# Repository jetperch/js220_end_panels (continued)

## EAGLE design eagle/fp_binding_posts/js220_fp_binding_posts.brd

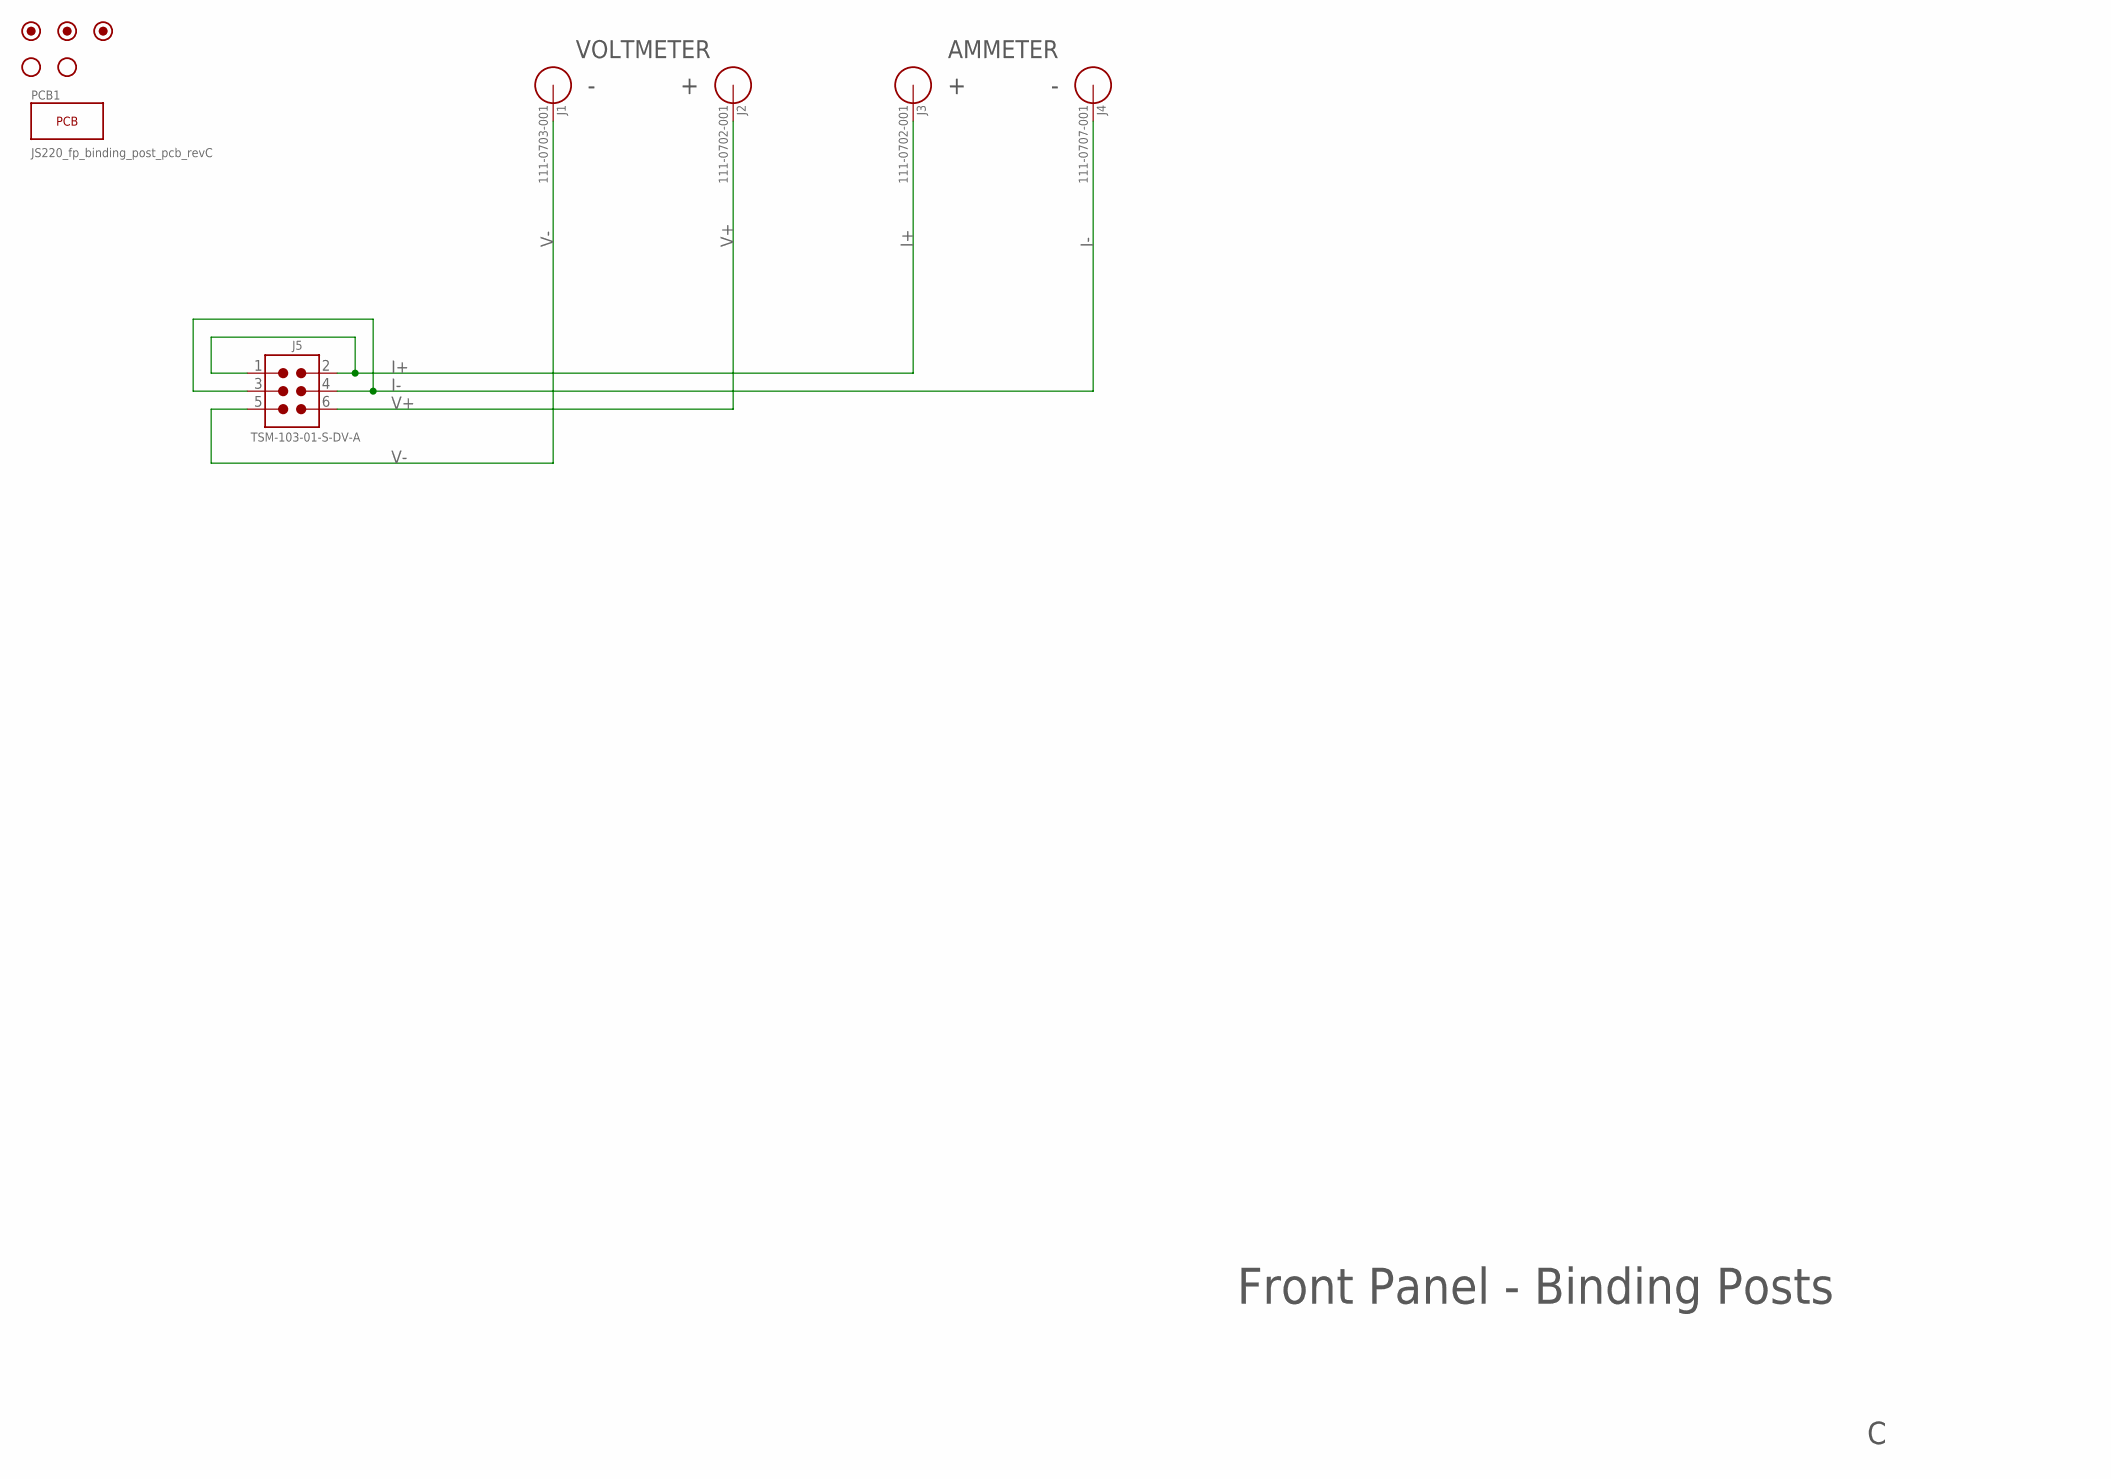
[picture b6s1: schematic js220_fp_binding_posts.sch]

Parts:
FUD1, FUD2, FUD3: FIDUCIAL_1MM; FIDUCIAL_1MM_2MM
H1, H2: HOLE_#6_NORESTRICT; HOLE_3.5MM_NORESTRICT
J1: 111-0703-001; BINDING_POST_6; MPN 111-0703-001
J2, J3: 111-0702-001; BINDING_POST_6; MPN 111-0702-001
J4: 111-0707-001; BINDING_POST_6; MPN 111-0707-001
J5: TSM-103-01-S-DV-A; CONN_0.1_3X2_MSA; MPN TSM-103-01-S-DV-A

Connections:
I+: J3.1, J5.1, J5.2
I-: J4.1, J5.3, J5.4
V+: J2.1, J5.6
V-: J1.1, J5.5

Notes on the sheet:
Front Panel - Binding Posts
+ -
AMMETER
VOLTMETER
- +

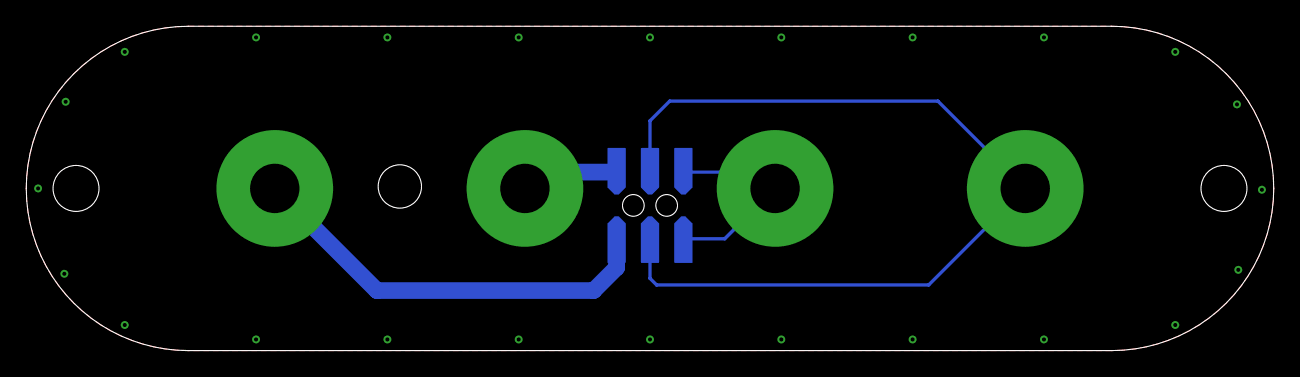
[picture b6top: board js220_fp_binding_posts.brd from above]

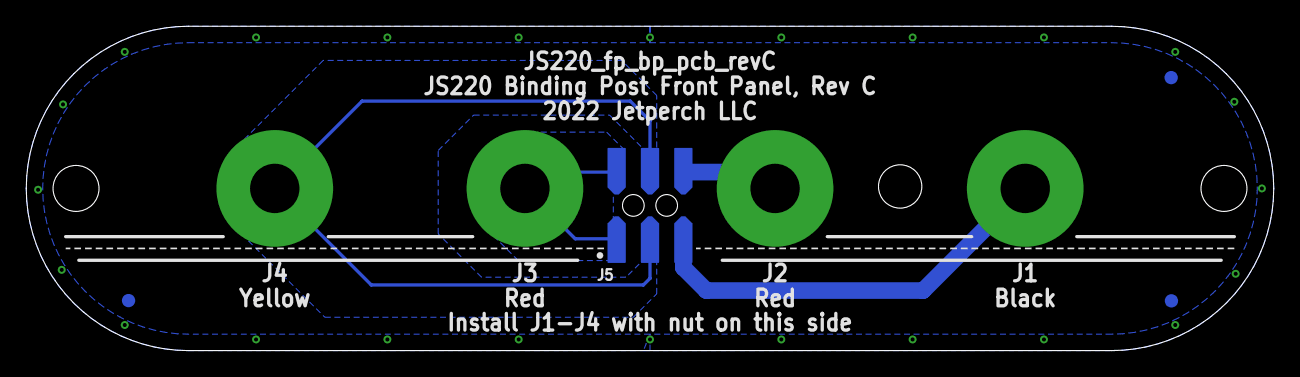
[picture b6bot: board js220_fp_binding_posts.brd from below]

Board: 2 copper layers, 95.0 x 24.7 mm, 10 parts (4 on the bottom side), 4 nets.

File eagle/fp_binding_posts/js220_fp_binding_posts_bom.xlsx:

BOM - All
2022 June 16
# | Qty | Ref Des | Name
1 | 2 | J2, J3 | 111-0702-001
2 | 1 | J1 | 111-0703-001
3 | 1 | J4 | 111-0707-001
4 | 1 | J5 | TSM-103-01-S-DV-A
5 | 1 | PCB1 | JS220_fp_binding_post_pcb_revC
 | 6

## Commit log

2021-07-23 Completed revA for the initial end panels.
    * Binding post front panel.
    * Back panel.
2022-02-12 Updated for p3
2022-02-12 Updated to rev B.
2022-02-17 Updated back panel.
2022-02-17 Updated for JS220 p3.
2022-02-25 Final build files.
    Fixed fp_binding_posts with corrected connector.
2022-07-01 Updated for beta build.
2022-09-15 Updates for JS220 first production build.
    * Updated back panel for production build.
    * Increased USB hole size by 0.2 mm in left, right, and up directions
    * Bumped rev from C to D.
    * Added additional boards:
    * fb_usb2_ba: USB 2.0 B/A connector
    * fp_bnc: BNC & 0.1" headers
2022-09-28 Fixed fb_usb2_ba connector A USB connector holes.
2022-10-03 Improved fp_baseline.
    * Added dimensions for all features.
    * Added chassis ground comment.
    * Added PDF.
    * First public release.
2022-10-03 Added PCBWay order example.
2022-10-04 Updated front panel baseline with additional dimensions and detail.
2022-10-06 Add initial KiCAD 6.0 fp_baseline, including .gitignore and notes
2022-10-23 Added connector part number to README.
2022-10-23 Fixed README space.
2022-10-26 fix front copper polygon so it acts as prper copper pour around pads
2022-11-14 Fix wrong pin numbering on JS220 panel symbol and update schematic to match
2023-11-14 Added safety banana jack front panel.
2024-01-12 Renamed js220_fp_banana to js220_fp_sba
2024-10-16 Added safety banana jack rev B with same connectors as JS110
2024-10-29 Added JS220 Safety Banana Jack front panel.
    Fixed connector part numbers for BOM.
